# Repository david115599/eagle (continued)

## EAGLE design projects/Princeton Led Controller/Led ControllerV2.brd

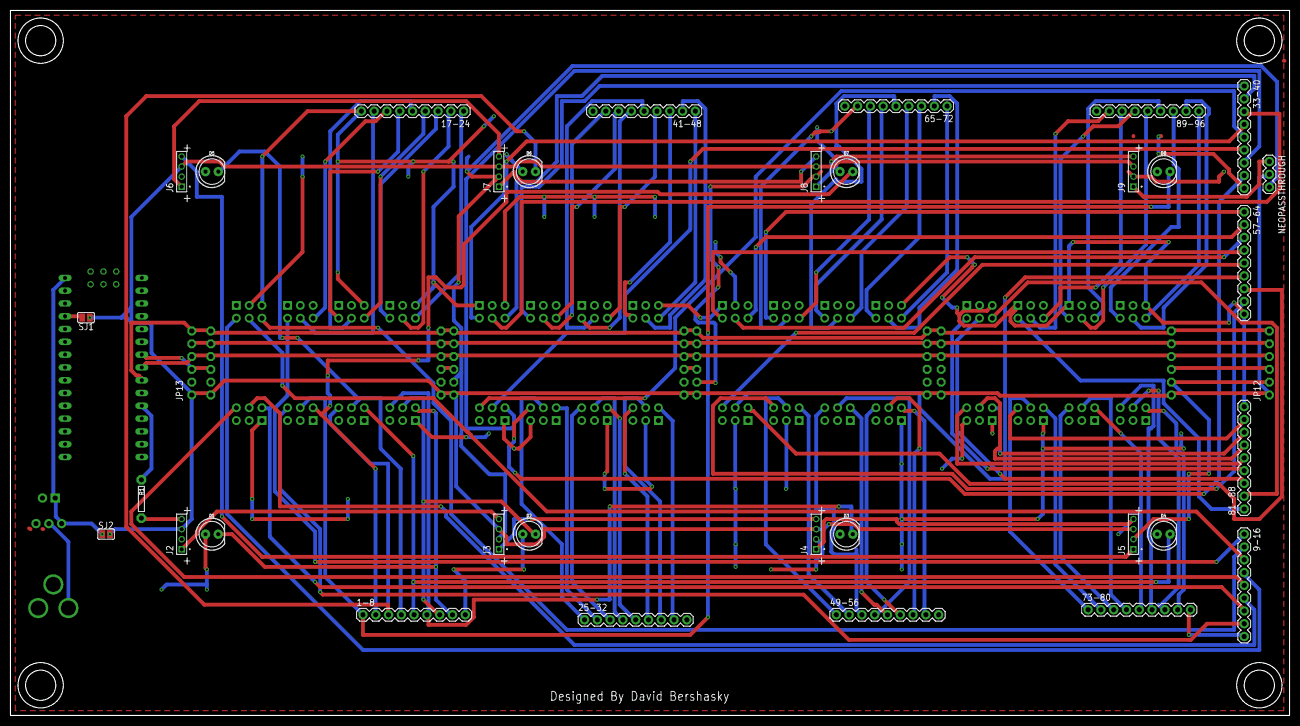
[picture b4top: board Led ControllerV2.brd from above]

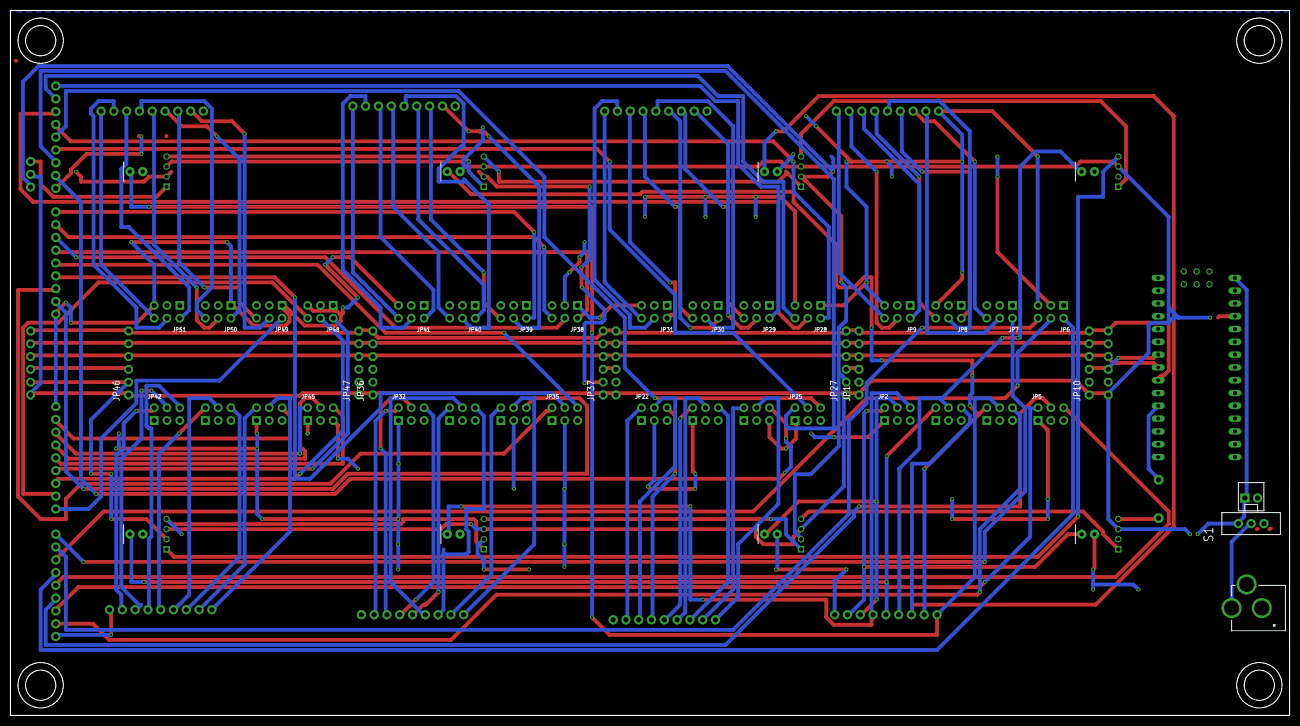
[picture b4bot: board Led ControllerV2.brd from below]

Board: 2 copper layers, 254.0 x 140.0 mm, 78 parts (44 on the bottom side), 119 nets.

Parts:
1-8, 9-16, 17-24, 25-32, 33-40, 41-48, 49-56, 57-64, 65-72, 73-80, 81-88, 89-96: M09; 1X09
D1, D2, D3, D4, D5, D6, D7, D8: LED_5MM
J1: POWER_JACKPTH; POWER_JACK_PTH
J2, J3, J4, J5, J6, J7, J8, J9: 62000411121
JP1, JP12, JP13, JP26, JP36, JP46: INPUT; 1X06-CLEANBIG
JP2, JP3, JP4, JP5, JP6, JP7, JP8, JP9, JP22, JP23, JP24, JP25, JP28, JP29, JP30, JP31, JP32, JP33, JP34, JP35, JP38, JP39, JP40, JP41, JP42, JP43, JP44, JP45, JP48, JP49, JP50, JP51: 2X03_ROUND_70MIL
JP10, JP27, JP37, JP47: OUTPUT; 1X06-CLEANBIG
JP11: MOLEX-1X2
NEOPASSTHROUGH: 1X03
R1: 300; AXL-REGULAR
S1: SWITCH-SPDT
SJ1, SJ2: SJW
U$1: NANO

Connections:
/OE: JP1.5, JP10.5, JP12.5, JP13.5, JP26.5, JP27.5, JP36.5, JP37.5, JP46.5, JP47.5
BAT+: J1.PWR, S1.2
CLK: JP1.4, JP10.4, JP12.4, JP13.4, JP26.4, JP27.4, JP36.4, JP37.4, JP46.4, JP47.4, U$1.D5
DATAIN: J2.4, R1.2
DIN: JP10.3, JP13.3, U$1.D4
DIN1: JP1.3, JP27.3
DIN2: JP26.3, JP37.3
DN4: JP12.3, JP46.3
GND: J1.GND, J1.GNDBREAK, J2.2, J3.2, J4.2, J5.2, J6.2, J7.2, J8.2, J9.2, JP1.2, JP10.2, JP11.2, JP12.2, JP13.2, JP26.2, JP27.2, JP36.2, JP37.2, JP46.2, JP47.2, NEOPASSTHROUGH.3, U$1.GND, U$1.GND1
LAT: JP1.6, JP10.6, JP12.6, JP13.6, JP26.6, JP27.6, JP36.6, JP37.6, JP46.6, JP47.6, U$1.D6
LED1: 1-8.8, D1.K, JP2.2
LED2: 1-8.7, D2.K, JP2.4
LED3: 1-8.6, D3.K, JP2.6
LED4: 1-8.5, D4.K, JP3.2
LED5: 1-8.4, D5.K, JP3.4
LED6: 1-8.3, D6.K, JP3.6
LED7: 1-8.2, D7.K, JP4.2
LED8: 1-8.1, D8.K, JP4.4
LED9: 9-16.8, JP4.6
LED10: 9-16.7, JP5.2
LED11: 9-16.6, JP5.4
LED12: 9-16.5, JP5.6
LED13: 9-16.4, JP6.2
LED14: 9-16.3, JP6.4
LED15: 9-16.2, JP6.6
LED16: 9-16.1, JP7.2
LED17: 17-24.8, JP7.4
LED18: 17-24.7, JP7.6
LED19: 17-24.6, JP8.2
LED20: 17-24.5, JP8.4
LED21: 17-24.4, JP8.6
LED22: 17-24.3, JP9.2
LED23: 17-24.2, JP9.4
LED24: 17-24.1, JP9.6
LED25: 25-32.8, JP22.2
LED26: 25-32.7, JP22.4
LED27: 25-32.6, JP22.6
LED28: 25-32.5, JP23.2
LED29: 25-32.4, JP23.4
LED30: 25-32.3, JP23.6
LED31: 25-32.2, JP24.2
LED32: 25-32.1, JP24.4
LED33: 33-40.8, JP24.6
LED34: 33-40.7, JP25.2
LED35: 33-40.6, JP25.4
LED36: 33-40.5, JP25.6
LED37: 33-40.4, JP28.2
LED38: 33-40.3, JP28.4
LED39: 33-40.2, JP28.6
LED40: 33-40.1, JP29.2
LED41: 41-48.8, JP29.4
LED42: 41-48.7, JP29.6
LED43: 41-48.6, JP30.2
LED44: 41-48.5, JP30.4
LED45: 41-48.4, JP30.6
LED46: 41-48.3, JP31.2
LED47: 41-48.2, JP31.4
LED48: 41-48.1, JP31.6
LED49: 49-56.8, JP32.2
LED50: 49-56.7, JP32.4
LED51: 49-56.6, JP32.6
LED52: 49-56.5, JP33.2
LED53: 49-56.4, JP33.4
LED54: 49-56.3, JP33.6
LED55: 49-56.2, JP34.2
LED56: 49-56.1, JP34.4
LED57: 57-64.8, JP34.6
LED58: 57-64.7, JP35.2
LED59: 57-64.6, JP35.4
LED60: 57-64.5, JP35.6
LED61: 57-64.4, JP38.2
LED62: 57-64.3, JP38.4
LED63: 57-64.2, JP38.6
LED64: 57-64.1, JP39.2
LED65: 65-72.8, JP39.4
LED66: 65-72.7, JP39.6
LED67: 65-72.6, JP40.2
LED68: 65-72.5, JP40.4
LED69: 65-72.4, JP40.6
LED70: 65-72.3, JP41.2
LED71: 65-72.2, JP41.4
LED72: 65-72.1, JP41.6
LED73: 73-80.8, JP42.2
LED74: 73-80.7, JP42.4
LED75: 73-80.6, JP42.6
LED76: 73-80.5, JP43.2
LED77: 73-80.4, JP43.4
LED78: 73-80.3, JP43.6
LED79: 73-80.2, JP44.2
LED80: 73-80.1, JP44.4
LED81: 81-88.8, JP44.6
LED82: 81-88.7, JP45.2
LED83: 81-88.6, JP45.4
LED84: 81-88.5, JP45.6
LED85: 81-88.4, JP48.2
LED86: 81-88.3, JP48.4
LED87: 81-88.2, JP48.6
LED88: 81-88.1, JP49.2
LED89: 89-96.8, JP49.4
LED90: 89-96.7, JP49.6
LED91: 89-96.6, JP50.2
LED92: 89-96.5, JP50.4
LED93: 89-96.4, JP50.6
LED94: 89-96.3, JP51.2
LED95: 89-96.2, JP51.4
LED96: 89-96.1, JP51.6
LED+: 1-8.9, 9-16.9, 17-24.9, 25-32.9, 33-40.9, 41-48.9, 49-56.9, 57-64.9, 65-72.9, 73-80.9, 81-88.9, 89-96.9, D1.A, D2.A, D3.A, D4.A, D5.A, D6.A, D7.A, D8.A, JP2.1, JP2.3, JP2.5, JP3.1, JP3.3, JP3.5, JP4.1, JP4.3, JP4.5, JP5.1, JP5.3, JP5.5, JP6.1, JP6.3, JP6.5, JP7.1, JP7.3, JP7.5, JP8.1, JP8.3, JP8.5, JP9.1, JP9.3, JP9.5, JP22.1, JP22.3, JP22.5, JP23.1, JP23.3, JP23.5, JP24.1, JP24.3, JP24.5, JP25.1, JP25.3, JP25.5, JP28.1, JP28.3, JP28.5, JP29.1, JP29.3, JP29.5, JP30.1, JP30.3, JP30.5, JP31.1, JP31.3, JP31.5, JP32.1, JP32.3, JP32.5, JP33.1, JP33.3, JP33.5, JP34.1, JP34.3, JP34.5, JP35.1, JP35.3, JP35.5, JP38.1, JP38.3, JP38.5, JP39.1, JP39.3, JP39.5, JP40.1, JP40.3, JP40.5, JP41.1, JP41.3, JP41.5, JP42.1, JP42.3, JP42.5, JP43.1, JP43.3, JP43.5, JP44.1, JP44.3, JP44.5, JP45.1, JP45.3, JP45.5, JP48.1, JP48.3, JP48.5, JP49.1, JP49.3, JP49.5, JP50.1, JP50.3, JP50.5, JP51.1, JP51.3, JP51.5
unnamed: JP11.1, S1.1, SJ2.1, U$1.RAW
unnamed: J9.1, NEOPASSTHROUGH.1
unnamed: J2.1, J3.4
unnamed: J3.1, J4.4
unnamed: J4.1, J5.4
unnamed: J5.1, J6.4
unnamed: J6.1, J7.4
unnamed: J7.1, J8.4
unnamed: J8.1, J9.4
NEODATA1: R1.1, U$1.D8
VCC: J2.3, J3.3, J4.3, J5.3, J6.3, J7.3, J8.3, J9.3, JP1.1, JP10.1, JP12.1, JP13.1, JP26.1, JP27.1, JP36.1, JP37.1, JP46.1, JP47.1, NEOPASSTHROUGH.2, SJ1.1, SJ2.2
VCCNANO: SJ1.2, U$1.5V

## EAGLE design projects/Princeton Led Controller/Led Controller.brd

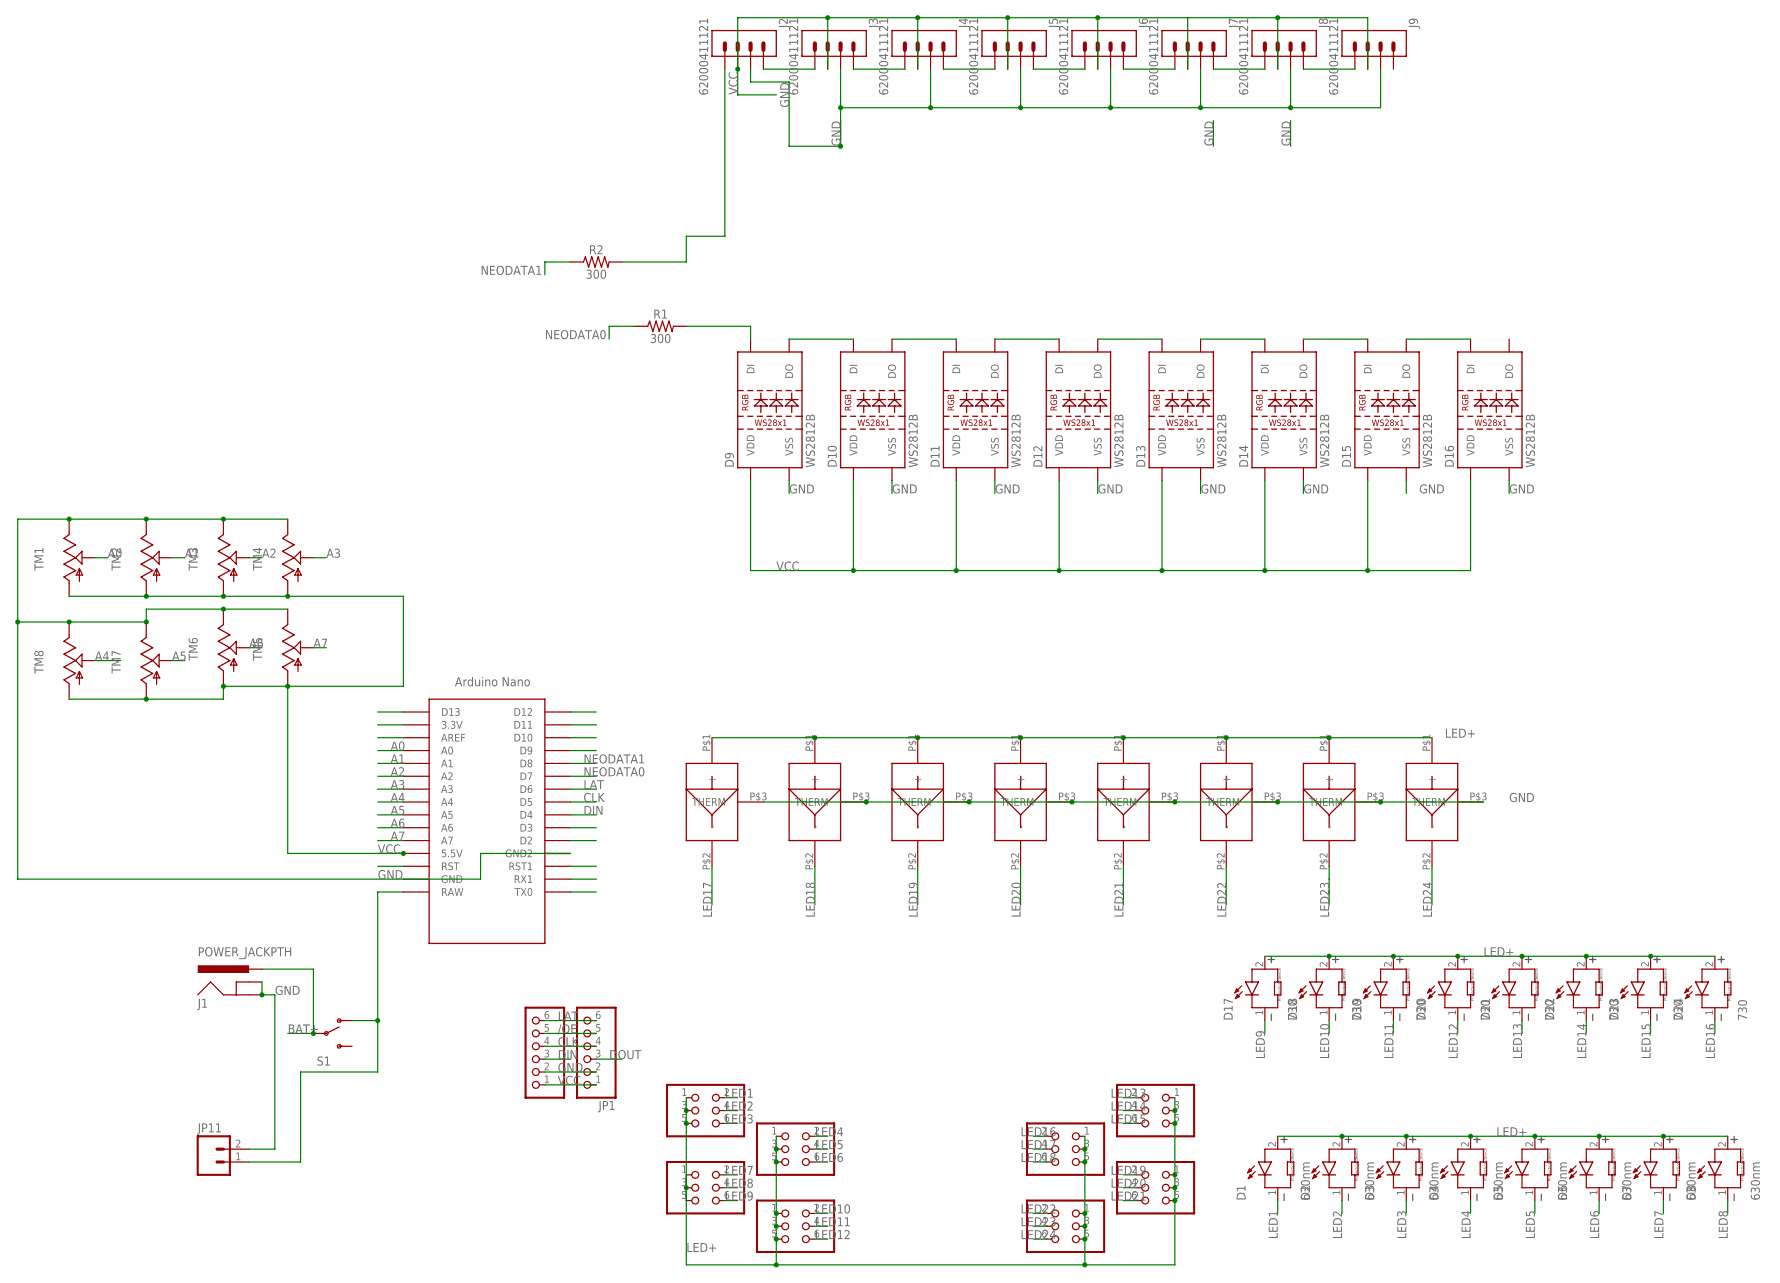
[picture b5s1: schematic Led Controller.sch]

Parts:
D1, D2, D3, D4, D5, D6, D7, D8: 630nm; WL-SWTC_3535
D9, D10, D11, D12, D13, D14, D15, D16: WS2812B; MPN WS2812B
D17, D18, D19, D20, D21, D22, D23, D24: 730; WL-SWTC_3535
J1: POWER_JACKPTH; POWER_JACK_PTH; MPN RAPC712BK
J2, J3, J4, J5, J6, J7, J8, J9: 62000411121
JP1: INPUT; 1X06-CLEANBIG; MPN 1016
JP2, JP3, JP4, JP5, JP6, JP7, JP8, JP9: HEADER-2X3; 2X03_ROUND_70MIL
JP10: OUTPUT; 1X06-CLEANBIG; MPN 1016
JP11: M02POLAR; MOLEX-1X2; MPN 171856-0002
R1, R2: 300; 0603; MPN MC0603SAF3000T5E
S1: SWITCH-SPSTPTH; SWITCH-SPDT; MPN 1825232-1
TM1, TM2, TM3, TM4, TM5, TM6, TM7, TM8: TRIM; 6MM; MPN 3306F-1-103
U$1: NANO
U$2, U$3, U$4, U$5, U$6, U$7, U$8, U$9: 2X2MMLED; 2X2LED

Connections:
/OE: JP1.5, JP10.5
A0: TM1.S, U$1.A0
A1: TM2.S, U$1.A1
A2: TM3.S, U$1.A2
A3: TM4.S, U$1.A3
A4: TM8.S, U$1.A4
A5: TM7.S, U$1.A5
A6: TM6.S, U$1.A6
A7: TM5.S, U$1.A7
BAT+: J1.PWR, S1.2
CLK: JP1.4, JP10.4, U$1.D5
DATAIN: J2.4, R2.2
DIN: JP10.3, U$1.D4
DOUT: JP1.3
GND: D9.3 (VSS), D10.3 (VSS), D11.3 (VSS), D12.3 (VSS), D13.3 (VSS), D14.3 (VSS), D15.3 (VSS), D16.3 (VSS), J1.GND, J1.GNDBREAK, J2.2, J3.2, J4.2, J5.2, J6.2, J7.2, J8.2, J9.2, JP1.2, JP10.2, JP11.2, TM1.E, TM2.E, TM3.E, TM4.E, TM5.E, TM6.E, TM7.E, TM8.E, U$1.GND, U$1.GND1 (GND2), U$2.P$3 (THERM), U$3.P$3 (THERM), U$4.P$3 (THERM), U$5.P$3 (THERM), U$6.P$3 (THERM), U$7.P$3 (THERM), U$8.P$3 (THERM), U$9.P$3 (THERM)
LAT: JP1.6, JP10.6, U$1.D6
LED1: D1.1, JP2.2
LED2: D2.1, JP2.4
LED3: D3.1, JP2.6
LED4: D4.1, JP3.2
LED5: D5.1, JP3.4
LED6: D6.1, JP3.6
LED7: D7.1, JP4.2
LED8: D8.1, JP4.4
LED9: D17.1, JP4.6
LED10: D18.1, JP5.2
LED11: D19.1, JP5.4
LED12: D20.1, JP5.6
LED13: D21.1, JP6.2
LED14: D22.1, JP6.4
LED15: D23.1, JP6.6
LED16: D24.1, JP7.2
LED17: JP7.4, U$2.P$2 (-)
LED18: JP7.6, U$3.P$2 (-)
LED19: JP8.2, U$4.P$2 (-)
LED20: JP8.4, U$5.P$2 (-)
LED21: JP8.6, U$6.P$2 (-)
LED22: JP9.2, U$7.P$2 (-)
LED23: JP9.4, U$8.P$2 (-)
LED24: JP9.6, U$9.P$2 (-)
LED+: D1.2, D2.2, D3.2, D4.2, D5.2, D6.2, D7.2, D8.2, D17.2, D18.2, D19.2, D20.2, D21.2, D22.2, D23.2, D24.2, JP2.1, JP2.3, JP2.5, JP3.1, JP3.3, JP3.5, JP4.1, JP4.3, JP4.5, JP5.1, JP5.3, JP5.5, JP6.1, JP6.3, JP6.5, JP7.1, JP7.3, JP7.5, JP8.1, JP8.3, JP8.5, JP9.1, JP9.3, JP9.5, U$2.P$1 (+), U$3.P$1 (+), U$4.P$1 (+), U$5.P$1 (+), U$6.P$1 (+), U$7.P$1 (+), U$8.P$1 (+), U$9.P$1 (+)
unnamed: JP11.1, S1.1 (O), U$1.RAW
unnamed: D9.2 (DO), D10.4 (DI)
unnamed: D10.2 (DO), D11.4 (DI)
unnamed: D11.2 (DO), D12.4 (DI)
unnamed: D12.2 (DO), D13.4 (DI)
unnamed: D13.2 (DO), D14.4 (DI)
unnamed: D14.2 (DO), D15.4 (DI)
unnamed: D15.2 (DO), D16.4 (DI)
unnamed: J2.1, J3.4
unnamed: J3.1, J4.4
unnamed: J4.1, J5.4
unnamed: D9.4 (DI), R1.2
unnamed: J5.1, J6.4
unnamed: J6.1, J7.4
unnamed: J7.1, J8.4
unnamed: J8.1, J9.4
NEODATA0: R1.1, U$1.D7
NEODATA1: R2.1, U$1.D8
VCC: D9.1 (VDD), D10.1 (VDD), D11.1 (VDD), D12.1 (VDD), D13.1 (VDD), D14.1 (VDD), D15.1 (VDD), D16.1 (VDD), J2.3, J3.3, J4.3, J5.3, J6.3, J7.3, J8.3, J9.3, JP1.1, JP10.1, TM1.A, TM2.A, TM3.A, TM4.A, TM5.A, TM6.A, TM7.A, TM8.A, U$1.5V (5.5V)

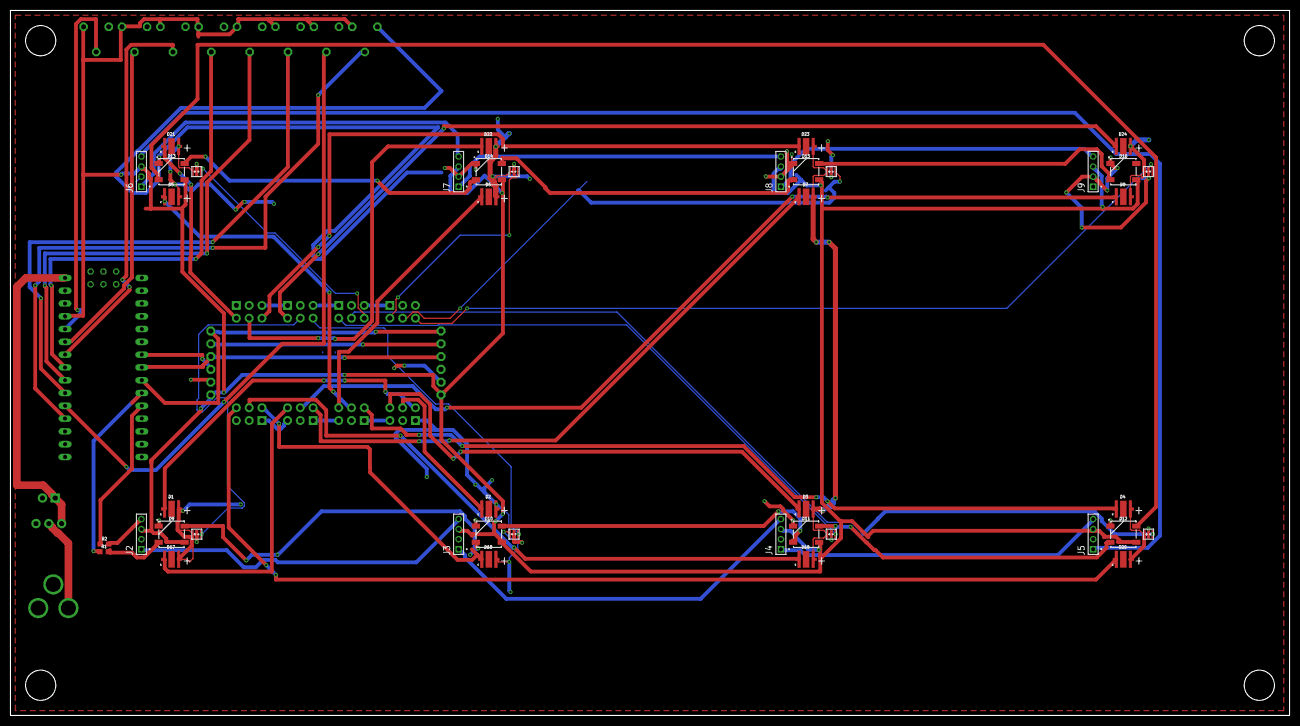
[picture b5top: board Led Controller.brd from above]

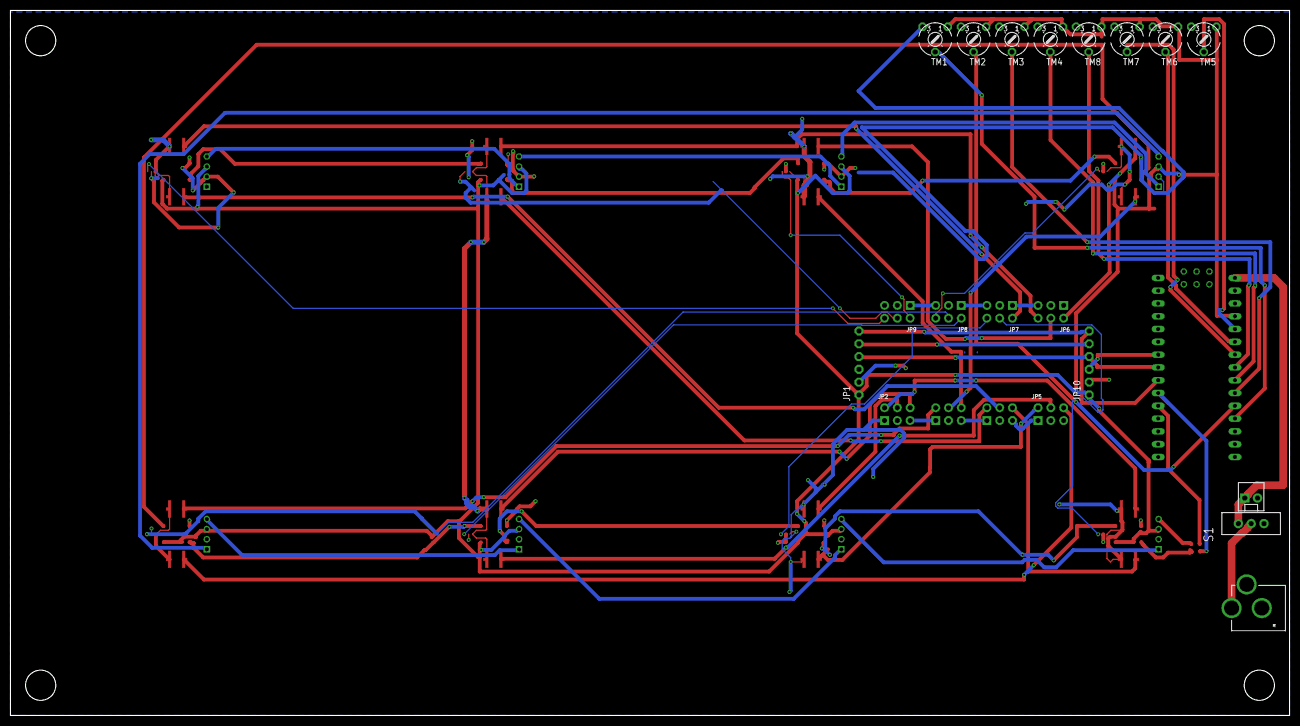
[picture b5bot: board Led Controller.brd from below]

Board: 2 copper layers, 254.0 x 140.0 mm, 64 parts (22 on the bottom side), 59 nets.

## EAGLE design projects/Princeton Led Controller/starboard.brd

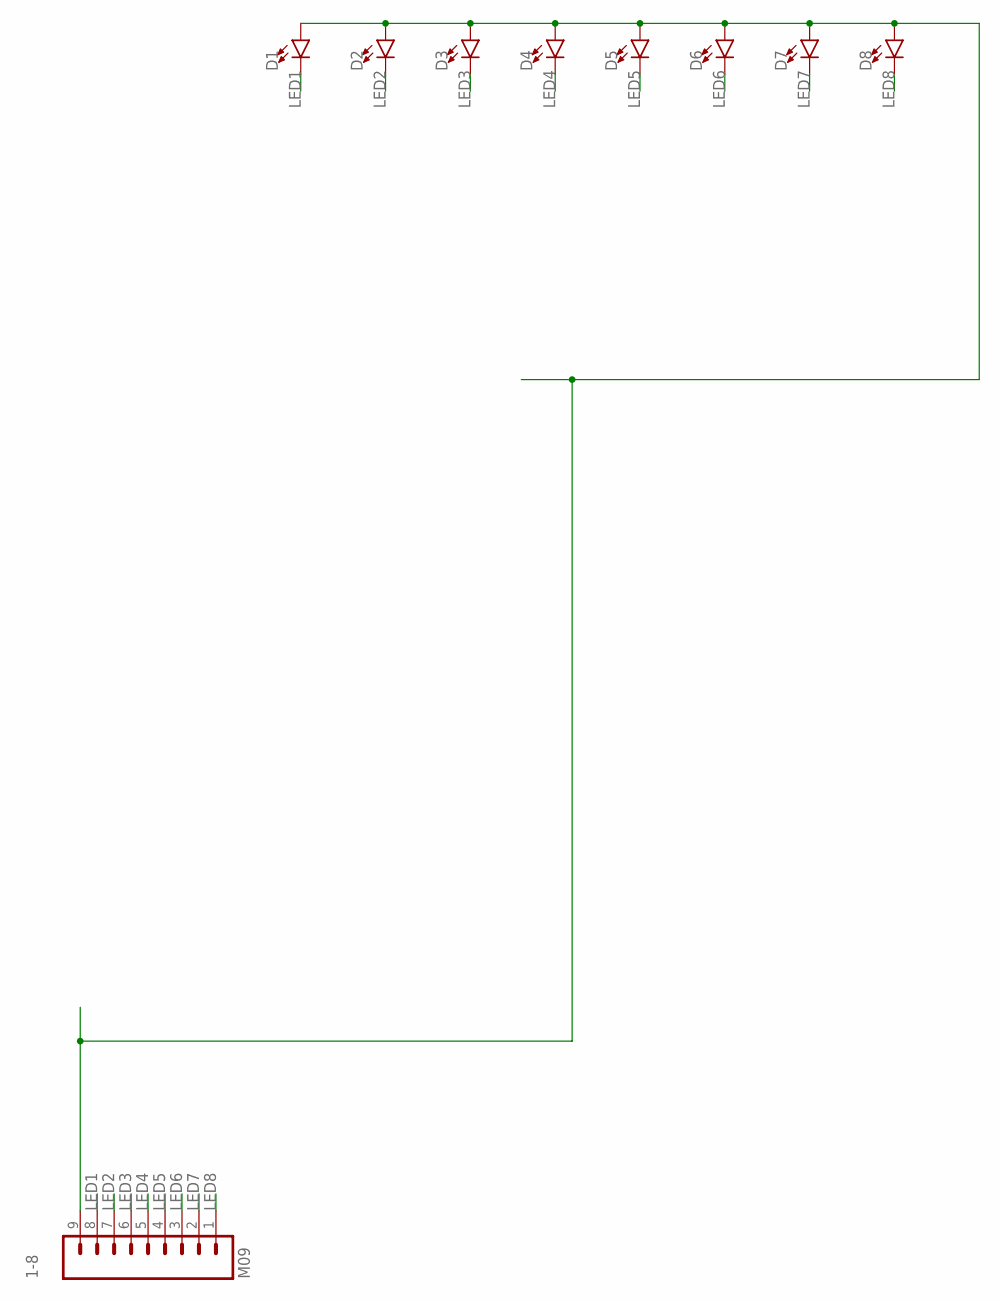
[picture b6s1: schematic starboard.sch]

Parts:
1-8: M09; 1X09
D1, D2, D3, D4, D5, D6, D7, D8: LED5MM; LED_5MM

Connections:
LED1: 1-8.8, D1.K (C)
LED2: 1-8.7, D2.K (C)
LED3: 1-8.6, D3.K (C)
LED4: 1-8.5, D4.K (C)
LED5: 1-8.4, D5.K (C)
LED6: 1-8.3, D6.K (C)
LED7: 1-8.2, D7.K (C)
LED8: 1-8.1, D8.K (C)
LED+: 1-8.9, D1.A, D2.A, D3.A, D4.A, D5.A, D6.A, D7.A, D8.A

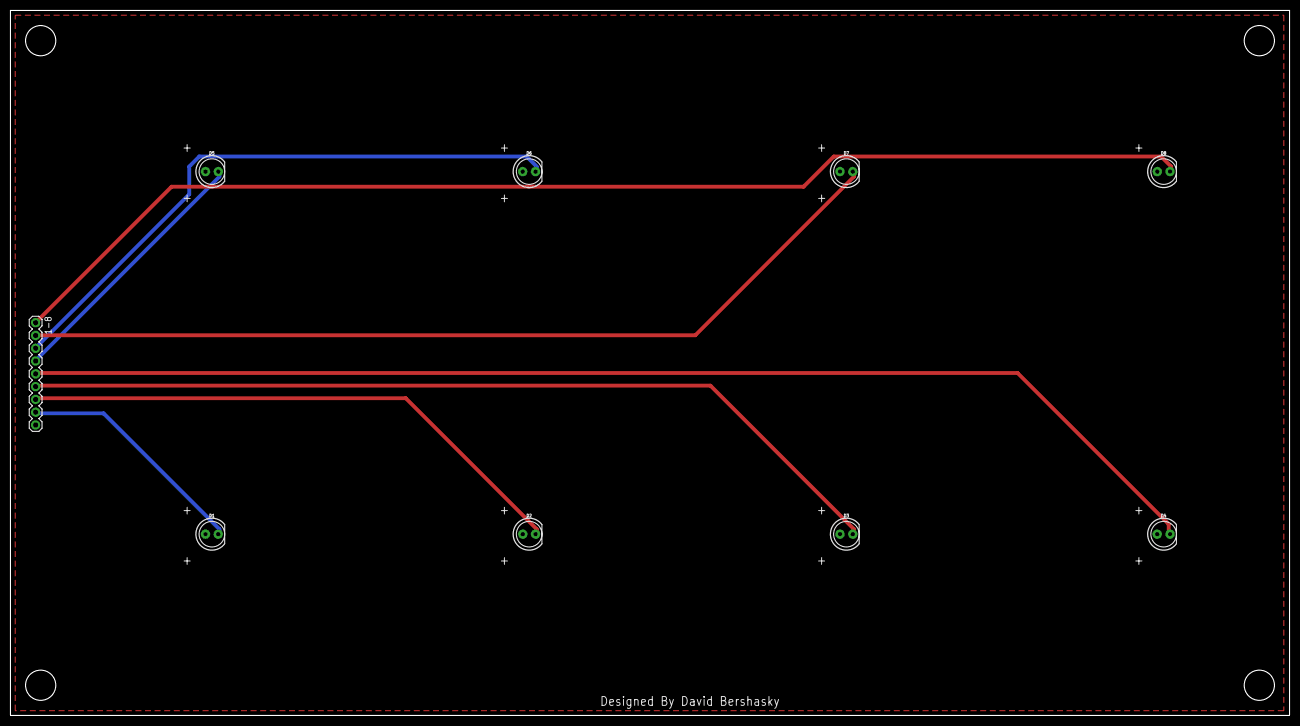
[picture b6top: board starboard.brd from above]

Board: 2 copper layers, 254.0 x 140.0 mm, 9 parts (0 on the bottom side), 9 nets.

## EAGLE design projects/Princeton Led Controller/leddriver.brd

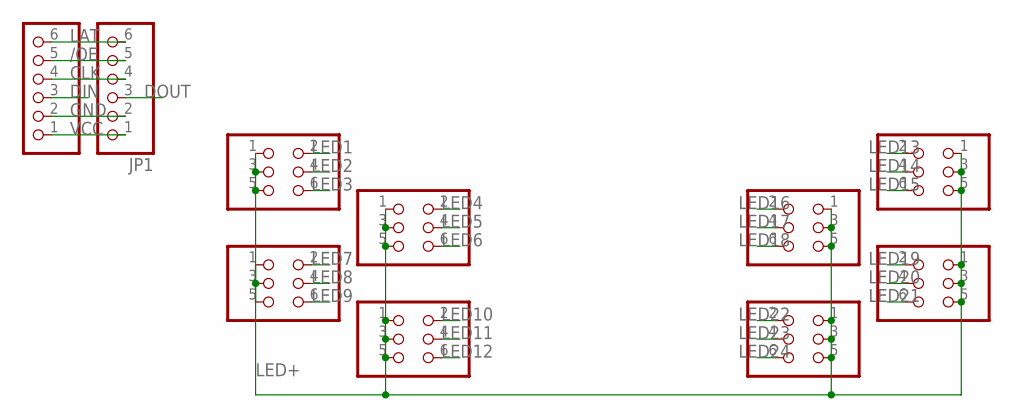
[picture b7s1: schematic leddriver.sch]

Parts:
JP1: INPUT; 1X06-CLEANBIG; MPN 1016
JP2, JP3, JP4, JP5, JP6, JP7, JP8, JP9: HEADER-2X3; 2X03_ROUND_70MIL
JP10: OUTPUT; 1X06-CLEANBIG; MPN 1016

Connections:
/OE: JP1.5, JP10.5
CLK: JP1.4, JP10.4
DIN: JP10.3
DOUT: JP1.3
GND: JP1.2, JP10.2
LAT: JP1.6, JP10.6
LED1: JP2.2
LED2: JP2.4
LED3: JP2.6
LED4: JP3.2
LED5: JP3.4
LED6: JP3.6
LED7: JP4.2
LED8: JP4.4
LED9: JP4.6
LED10: JP5.2
LED11: JP5.4
LED12: JP5.6
LED13: JP6.2
LED14: JP6.4
LED15: JP6.6
LED16: JP7.2
LED17: JP7.4
LED18: JP7.6
LED19: JP8.2
LED20: JP8.4
LED21: JP8.6
LED22: JP9.2
LED23: JP9.4
LED24: JP9.6
LED+: JP2.1, JP2.3, JP2.5, JP3.1, JP3.3, JP3.5, JP4.1, JP4.3, JP4.5, JP5.1, JP5.3, JP5.5, JP6.1, JP6.3, JP6.5, JP7.1, JP7.3, JP7.5, JP8.1, JP8.3, JP8.5, JP9.1, JP9.3, JP9.5
VCC: JP1.1, JP10.1

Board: 2 copper layers, 10 parts (10 on the bottom side), 6 nets, no tracks yet.

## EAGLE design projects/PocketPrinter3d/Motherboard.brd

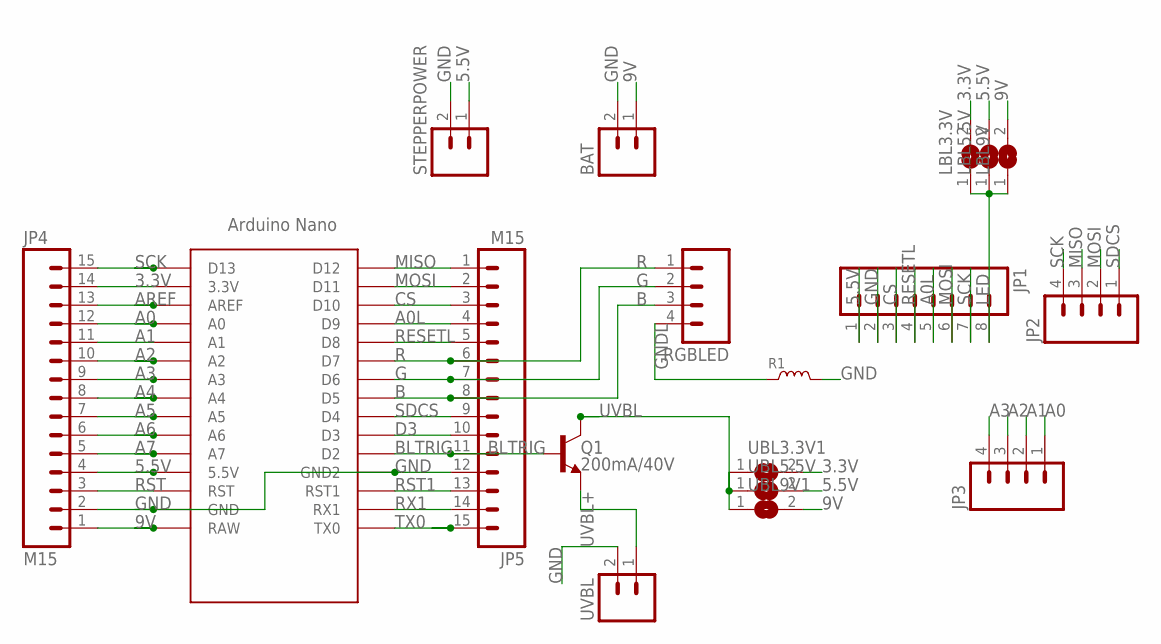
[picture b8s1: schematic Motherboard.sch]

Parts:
BAT: M02PTH; 1X02
JP1: M08; 1X08
JP2, JP3: M04PTH; 1X04
JP4, JP5: M15; 1X15
LBL3.3V, LBL5.5V, LBL9V: JUMPER; SJW
Q1: 200mA/40V; TO-92
R1: COIL-AXL-REGULAR; AXL-REGULAR
RGBLED: M04PTH; 1X04
STEPPERPOWER: M02PTH; 1X02
U$1: NANO
UBL3.3V1, UBL5.5V, UBL9V1: JUMPER; SJW
UVBL: M02LOCK; 1X02_LOCK

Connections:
3.3V: JP4.14, LBL3.3V.2, U$1.3.3V, UBL3.3V1.2
5.5V: JP1.1, JP4.4, LBL5.5V.2, STEPPERPOWER.1, U$1.5V (5.5V), UBL5.5V.2
9V: BAT.1, JP4.1, LBL9V.2, U$1.RAW, UBL9V1.2
A0: JP3.1, JP4.12, U$1.A0
A0L: JP1.5, JP5.4, U$1.D9
A1: JP3.2, JP4.11, U$1.A1
A2: JP3.3, JP4.10, U$1.A2
A3: JP3.4, JP4.9, U$1.A3
A4: JP4.8, U$1.A4
A5: JP4.7, U$1.A5
A6: JP4.6, U$1.A6
A7: JP4.5, U$1.A7
AREF: JP4.13, U$1.AREF
B: JP5.8, RGBLED.3, U$1.D5
BLTRIG: JP5.11, Q1.2 (B), U$1.D2
CS: JP1.3, JP5.3, U$1.D10
D3: JP5.10, U$1.D3
G: JP5.7, RGBLED.2, U$1.D6
GND: BAT.2, JP1.2, JP4.2, JP5.12, R1.2, STEPPERPOWER.2, U$1.GND, U$1.GND1 (GND2), UVBL.2
GNDL: R1.1, RGBLED.4
LED: JP1.8, LBL3.3V.1, LBL5.5V.1, LBL9V.1
MISO: JP2.3, JP5.1, U$1.D12
MOSI: JP1.6, JP2.2, JP5.2, U$1.D11
R: JP5.6, RGBLED.1, U$1.D7
RESETL: JP1.4, JP5.5, U$1.D8
RST: JP4.3, U$1.RST
RST1: JP5.13, U$1.RST1
RX1: JP5.14, U$1.RX1
SCK: JP1.7, JP2.4, JP4.15, U$1.D13
SDCS: JP2.1, JP5.9, U$1.D4
TX0: JP5.15, U$1.TX0
UVBL: Q1.3 (C), UBL3.3V1.1, UBL5.5V.1, UBL9V1.1
UVBL+: Q1.1 (E), UVBL.1

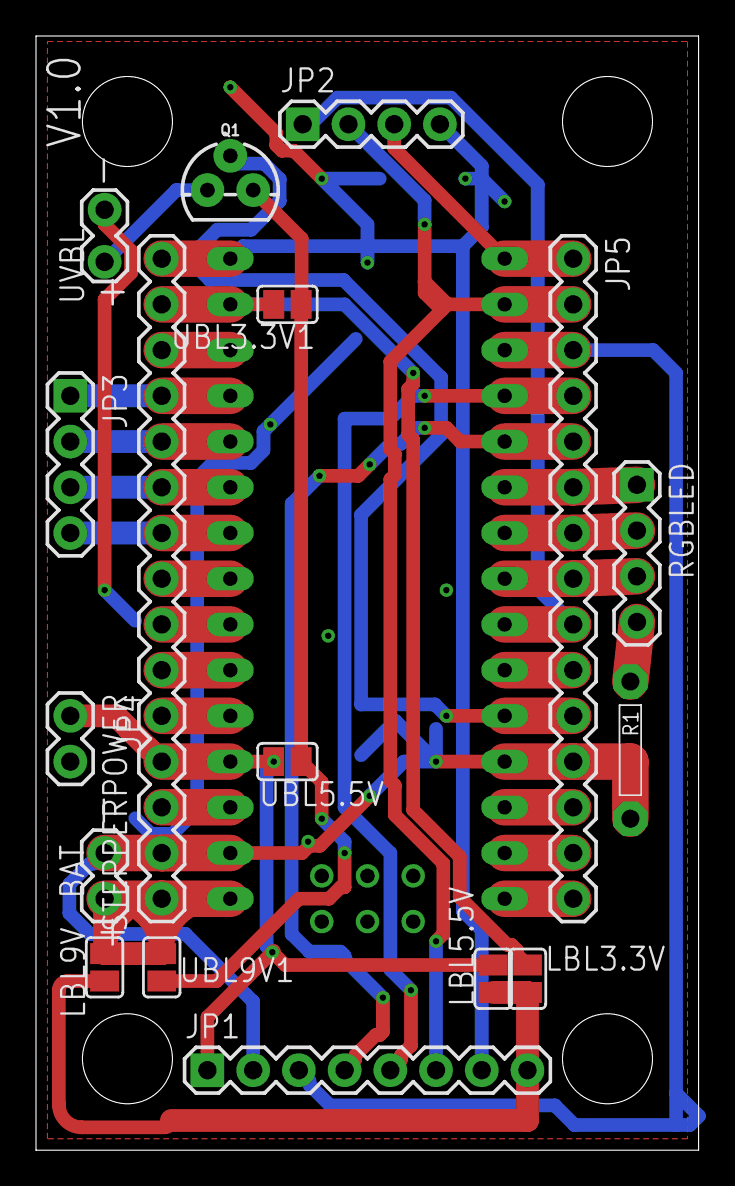
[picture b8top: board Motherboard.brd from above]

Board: 2 copper layers, 36.8 x 61.9 mm, 18 parts (0 on the bottom side), 33 nets.

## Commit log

2017-09-05 sad
    And
2017-09-07 sd
    sd
2017-09-07 k
    K
2017-09-08 dfg
    dfg
2017-09-08 nk
    kk
2017-09-08 asdsa
    asd
2017-09-08 hjds
    Sehfdgs
2017-09-08 Ads
    And
2017-09-08 And
    asd
2017-09-18 asd
    And
2017-09-19 asd
    asd
2017-09-19 sad
    sd
2017-09-25 And
    And
2017-10-05 as
    as
2017-10-05 j
    J
2017-10-06 And
    Sad
2017-10-07 d
    d
2017-10-10 asd
    Sd
2017-10-11 m
    m
2017-10-11 S
    Ss
2017-10-12 S
    S
2017-10-12 z
    Z
2017-10-17 M
    Mm
2017-10-26 k
    J
2017-10-27 q
    q
2017-11-01 K
    M
2017-11-01 q
    A
2017-11-01 a
    a
2017-11-10 n
    N
2017-11-10 x
    x
2017-11-10 Revert "s"
    This reverts commit f00e3bdaf57eb9e1bba398a63e28bb58f9eab196.
2017-11-10 .
    .
2017-11-14 ,
    M
2017-11-29 Changes detailed in email
2017-12-01 jh
    M
2017-12-03 Fully routed and all parts in
2017-12-03 added resistors
2017-12-03 Misc Changes
2017-12-03 Removed BOM -- new one on Google Drive
2017-12-03 M
    N
2017-12-05 kk
    Kk
2017-12-05 Z
    x
2017-12-07 ;
    ,
2018-04-23 Revert "Jn"
    This reverts commit 949b55ac397965d5a62205a9cf1140886c4f9a88.
2018-04-23 Revert "d"
    This reverts commit 945acfae5977ab3288e16057e6301ab493dab737.
2018-04-23 Revert "Revert "Jn""
    This reverts commit 1ae948dd20d83fe81bf3802b55d69c07987e5727.
2018-04-23 Revert "a"
    This reverts commit 4d56449c269a8bc0a96c68d2fbf7ca2c911cc7a2.
2018-04-23 y
    u
2018-04-28 f
    D
2018-06-06 ,
    ,
2018-06-26 m
    ,
2018-07-04 sd
    asdsa
2018-09-05 a
    s
2018-09-19 .
    ,
2019-03-11 fghjk
    vb
2019-04-14 kljn
    jk
2019-04-23 asdsad
    asdsad
2019-07-12 sada
    ds
2019-08-12 nlm
    m.,
2019-09-05 g
    b
2019-09-06 h
    j
2019-10-07 sad
    asd
2019-11-15 asd
    sad
2020-02-06 populated m.2 schematic
2020-02-06 added m.2 port for gsm
2020-06-03 bnm
    vbh
2020-06-06 asdsad
    asdsadasd
2020-07-03 wqed
    afs
2020-10-16 sdf
    dfs
